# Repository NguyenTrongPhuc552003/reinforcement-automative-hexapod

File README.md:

## NOTE: This hexapod project is still under development and may not be fully functional. So, please wait for an official release is coming soon!

# Hexapod Robot Control System

A comprehensive control system for a six-legged robot (hexapod) using BeagleBone AI (or Black), featuring both kernel-space drivers and user-space applications with reinforcement learning capabilities.

<div align="center">

</div>

## Project Overview

This project implements a complete software stack for controlling a 6-legged robot with 18 servo motors (3 per leg), including:

- **Kernel-Space Components**:
  - Linux kernel driver for servo control (PCA9685 PWM controllers)
  - IMU sensor driver (MPU6050) for orientation sensing
  - Hardware abstraction layer for unified device access
  
- **User-Space Components**: 
  - Kinematics library for precise leg positioning
  - Gait generation for various walking patterns
  - Calibration system for mechanical offset compensation
  - Interactive control interface

- **Reinforcement Learning**:
  - TD3 (Twin Delayed Deep Deterministic Policy Gradient) implementation
  - Hardware acceleration via TIDL and OpenCL
  - Simulation-to-real transfer capabilities
  - On-robot inference engine

## System Architecture

The system follows a layered architecture with hardware abstraction. For visual reference, see the architecture diagrams in the `/docs/diagram/image` directory:

- [Deployment Diagram](docs/diagram/image/deployment.png): Hardware and software deployment
- [Component Diagram](docs/diagram/image/component.png): Hardware component interactions
- [Sequence Diagram](docs/diagram/image/sequence.png): Runtime interactions
- [State Diagram](docs/diagram/image/state.png): Hardware state transitions
- [Class Diagram](docs/diagram/image/class.png): Software class structure
- [Building Process](docs/diagram/image/building.png): Build and deployment process

```t
.
├── driver/          # Linux kernel device drivers
├── app/             # User applications and libraries
├── docs/            # Documentation
└── scripts/         # Build and utility scripts
```

## Features

- Multiple gait patterns (tripod, wave, ripple)
- Real-time IMU feedback
- Inverse kinematics for precise leg control
- Hardware abstraction layer
- Comprehensive test suite
- Interactive debugging tools

## Prerequisites

- BeagleBone Black (Rev C) running Linux Kernel 5.10+
- I2C enabled (bus 2)
- 18x servo motors (MG996R recommended)
- 1x MPU6050 IMU sensor
- 2x PCA9685 PWM controllers

## Quick Start

1. Build the kernel module:
   ```bash
   ./scripts/build.sh -b driver
   ```

2. Install the kernel module on BeagleBone Black:
   ```bash
   ./install.sh
   ```

3. Build user-space applications:
   ```bash
   ./scripts/build.sh -b app
   ```

4. Run the test utility on BeagleBone Black:
   ```bash
   ./test_servo
   ```

## Development

See individual README files in subdirectories for detailed development guides:
- [Kernel Driver README](driver/README.md)
- [User Space README](app/README.md)
- [Python TD3 README](pytd3/README.md)
- [Hardware Overview README](hardware/README.md)
- [Cross-compile Environment README](docker/README.md)
- [Documentation](docs/README.md)

## Testing

Individual tests:
```bash
./test_servo       # Test servo control
./test_mpu6050     # Test IMU sensor
./test_autonomous  # Test autonomous navigation
./test_calibration # Test servos offset for each leg
./test_hcsr04      # Test HC-SR04 sensor
```

## Troubleshooting

### Sensor Issues
- **Zero IMU readings**: The MPU6050 enters sleep mode to save power. The driver now automatically wakes it before readings.
- **Erratic IMU behavior**: Check I2C connections and ensure proper power supply voltage.

### Servo Issues
- **Servos not moving**: Check power supply and ensure driver is properly loaded
- **Erratic movement**: Verify calibration settings and check for loose connections

## Documentation

- [Hardware Setup](docs/overview/hardware.md)
- [Software Architecture](docs/overview/architecture.md)
- [Quick Start Guide](docs/overview/quickstart.md)

## Contributing

1. Fork the repository
2. Create a feature branch
3. Commit your changes
4. Push to the branch
5. Create a Pull Request

## License

This project is licensed under the terms of the GNU General Public License v2.0.

## Authors

- StrongFood - I mean **"TrongPhuc"**

## Acknowledgments

- BeagleBoard.org
- Linux Kernel Community

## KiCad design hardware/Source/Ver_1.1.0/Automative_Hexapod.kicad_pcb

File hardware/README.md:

## System Components

### 1. **BeagleBone Black (BBB)**
BeagleBone Black is used as the central processing unit, running Linux and handling all real-time control logic. It communicates with:
- **PCA9685 servo drivers** via I2C (SCL on P9.19, SDA on P9.20)
- **Ultrasonic sensor** via GPIO (TRIG on P8.11, ECHO on P8.12)
- **IMU (MPU6050)** via I2C

It also generates PWM signals and controls other peripherals (e.g., thermal fan).

---

### 2. **Servo Driver Modules**
Two PCA9685 chips are used as PWM generators to drive 16 of the 18 required servos (expandable). Each driver:
- Communicates with the BBB over I2C
- Outputs 8 independent PWM signals for servo motors
- Includes address pins (A0–A5) to support multiple drivers on the same I2C bus
- Contains decoupling capacitors and pull-up resistors for signal stability

---

### 3. **Ultrasonic Sensor (HC-SR04)**
The HC-SR04 sensor is used to detect obstacles and measure distance:
- Powered by +5V with decoupling capacitors (10uF and 100nF)
- Connected to BBB via:
  - TRIG pin (output from BBB)
  - ECHO pin (input to BBB, with level shifting for 3.3V compatibility)
- The data is used to decide turning or stopping actions

---

### 4. **IMU Sensor (MPU6050)**
- Provides orientation and acceleration feedback
- Connected via I2C (shared with other peripherals)
- Powered by +5V with local decoupling capacitors

---

### 5. **Power Supply Circuit**
- Accepts external battery input (+BATT) and generates regulated +5V and +3.3V
- Features buck converter (TPS54331DR) with appropriate filter networks
- Provides stable voltage rails to all system modules

---

### 6. **Level Shifting Circuit**
- Used to safely interface 5V logic (from HC-SR04 ECHO) with 3.3V logic of the BBB
- Implemented using MOSFET-based bidirectional level shifters
- Ensures reliable operation and protection of BBB GPIO pins

---

### 7. **Thermal Fan Driver**
- Controlled via PWM from BBB (PWM1A)
- Includes MOSFET switching and resistive control for speed regulation
- Provides thermal management for the electronics chassis if needed

---

### 8. **Servo Connectors Board**
- Groups and distributes servo outputs from the PCA9685 modules
- Adds additional bypass capacitors for local noise suppression
- Organized with labeled connectors for easy assembly

---

## Files and Schematics
The full KiCad schematic set includes:
- `Overview Schematic`
- `BBBlack.kicad_sch`
- `ServoDrivers.kicad_sch`
- `HC-SR04.kicad_sch`
- `IMU.kicad_sch`
- `PowerSupply.kicad_sch`
- `LevelShifting.kicad_sch`
- `ThermalFan.kicad_sch`
- `ConnectorServo.kicad_sch`

---

## Key Features
- 18 DOF hexapod locomotion with coordinated servo control
- Real-time obstacle detection using HC-SR04
- Modular design with clean separation of power, control, and sensing
- Compatible with Linux-based development on BeagleBone Black

---

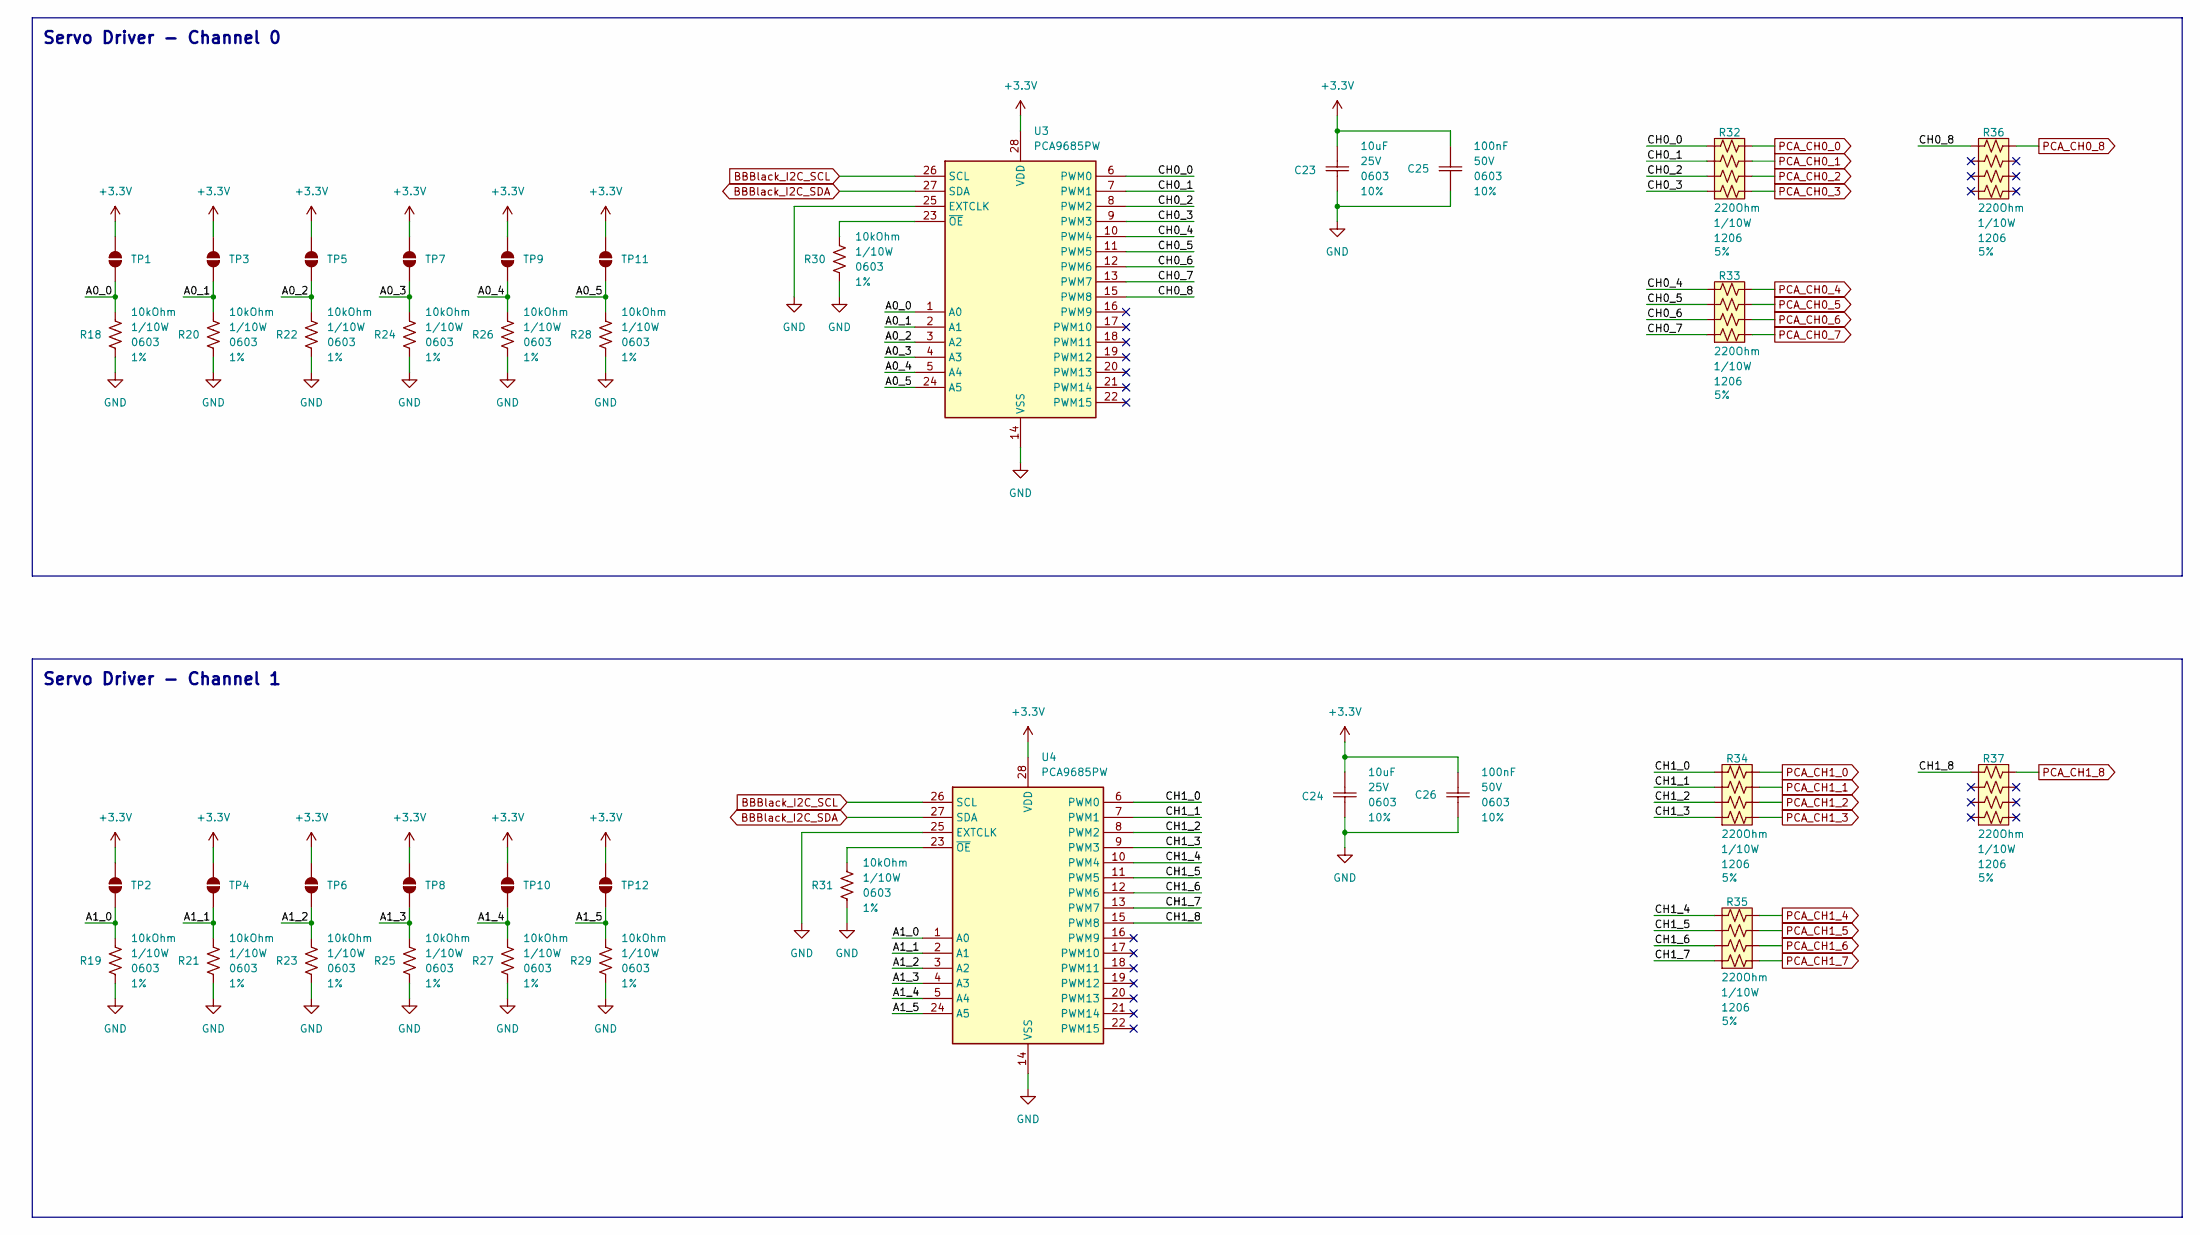
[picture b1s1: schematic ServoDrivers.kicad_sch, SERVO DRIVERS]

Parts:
C23, C24: 10uF; Ceramic_Cap_0603
C25, C26: 100nF; Ceramic_Cap_0603
R18, R19, R20, R21, R22, R23, R24, R25, R26, R27, R28, R29, R30, R31: 10kOhm; Res_0603
R32, R33, R34, R35, R36, R37: 220Ohm; R_Array_Convex_4x0603
TP1, TP2, TP3, TP4, TP5, TP6, TP7, TP8, TP9, TP10, TP11, TP12: SolderBridgeOpen
U3, U4: PCA9685PW; TSSOP-28_4.4x9.7mm_P0.65mm

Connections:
+3.3V: C23.2, C24.2, C25.2, C26.2, TP1.2, TP2.2, TP3.2, TP4.2, TP5.2, TP6.2, TP7.2, TP8.2, TP9.2, TP10.2, TP11.2, TP12.2, U3.28 (VDD), U4.28 (VDD); also elsewhere on the board
/Servo Drivers/A0_0: R18.2, TP1.1, U3.1 (A0)
/Servo Drivers/A0_1: R20.2, TP3.1, U3.2 (A1)
/Servo Drivers/A0_2: R22.2, TP5.1, U3.3 (A2)
/Servo Drivers/A0_3: R24.2, TP7.1, U3.4 (A3)
/Servo Drivers/A0_4: R26.2, TP9.1, U3.5 (A4)
/Servo Drivers/A0_5: R28.2, TP11.1, U3.24 (A5)
/Servo Drivers/A1_0: R19.2, TP2.1, U4.1 (A0)
/Servo Drivers/A1_1: R21.2, TP4.1, U4.2 (A1)
/Servo Drivers/A1_2: R23.2, TP6.1, U4.3 (A2)
/Servo Drivers/A1_3: R25.2, TP8.1, U4.4 (A3)
/Servo Drivers/A1_4: R27.2, TP10.1, U4.5 (A4)
/Servo Drivers/A1_5: R29.2, TP12.1, U4.24 (A5)
/Servo Drivers/CH0_0: R32.4, U3.6 (PWM0)
/Servo Drivers/CH0_1: R32.3, U3.7 (PWM1)
/Servo Drivers/CH0_2: R32.2, U3.8 (PWM2)
/Servo Drivers/CH0_3: R32.1, U3.9 (PWM3)
/Servo Drivers/CH0_4: R33.4, U3.10 (PWM4)
/Servo Drivers/CH0_5: R33.3, U3.11 (PWM5)
/Servo Drivers/CH0_6: R33.2, U3.12 (PWM6)
/Servo Drivers/CH0_7: R33.1, U3.13 (PWM7)
/Servo Drivers/CH0_8: R36.4, U3.15 (PWM8)
/Servo Drivers/CH1_0: R34.4, U4.6 (PWM0)
/Servo Drivers/CH1_1: R34.3, U4.7 (PWM1)
/Servo Drivers/CH1_2: R34.2, U4.8 (PWM2)
/Servo Drivers/CH1_3: R34.1, U4.9 (PWM3)
/Servo Drivers/CH1_4: R35.4, U4.10 (PWM4)
/Servo Drivers/CH1_5: R35.3, U4.11 (PWM5)
/Servo Drivers/CH1_6: R35.2, U4.12 (PWM6)
/Servo Drivers/CH1_7: R35.1, U4.13 (PWM7)
/Servo Drivers/CH1_8: R37.4, U4.15 (PWM8)
BBBlack_I2C_SCL: U3.26 (SCL), U4.26 (SCL); also elsewhere on the board
BBBlack_I2C_SDA: U3.27 (SDA), U4.27 (SDA); also elsewhere on the board
GND: C23.1, C24.1, C25.1, C26.1, R18.1, R19.1, R20.1, R21.1, R22.1, R23.1, R24.1, R25.1, R26.1, R27.1, R28.1, R29.1, R30.1, R31.1, U3.14 (VSS), U3.25 (EXTCLK), U4.14 (VSS), U4.25 (EXTCLK); also elsewhere on the board
unnamed: R30.2, U3.23 (~OE)
unnamed: R31.2, U4.23 (~OE)
PCA_CH0_0: R32.5; also elsewhere on the board
PCA_CH0_1: R32.6; also elsewhere on the board
PCA_CH0_2: R32.7; also elsewhere on the board
PCA_CH0_3: R32.8; also elsewhere on the board
PCA_CH0_4: R33.5; also elsewhere on the board
PCA_CH0_5: R33.6; also elsewhere on the board
PCA_CH0_6: R33.7; also elsewhere on the board
PCA_CH0_7: R33.8; also elsewhere on the board
PCA_CH0_8: R36.5; also elsewhere on the board
PCA_CH1_0: R34.5; also elsewhere on the board
PCA_CH1_1: R34.6; also elsewhere on the board
PCA_CH1_2: R34.7; also elsewhere on the board
PCA_CH1_3: R34.8; also elsewhere on the board
PCA_CH1_4: R35.5; also elsewhere on the board
PCA_CH1_5: R35.6; also elsewhere on the board
PCA_CH1_6: R35.7; also elsewhere on the board
PCA_CH1_7: R35.8; also elsewhere on the board
PCA_CH1_8: R37.5; also elsewhere on the board

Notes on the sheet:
Servo Driver - Channel 1
Servo Driver - Channel 0

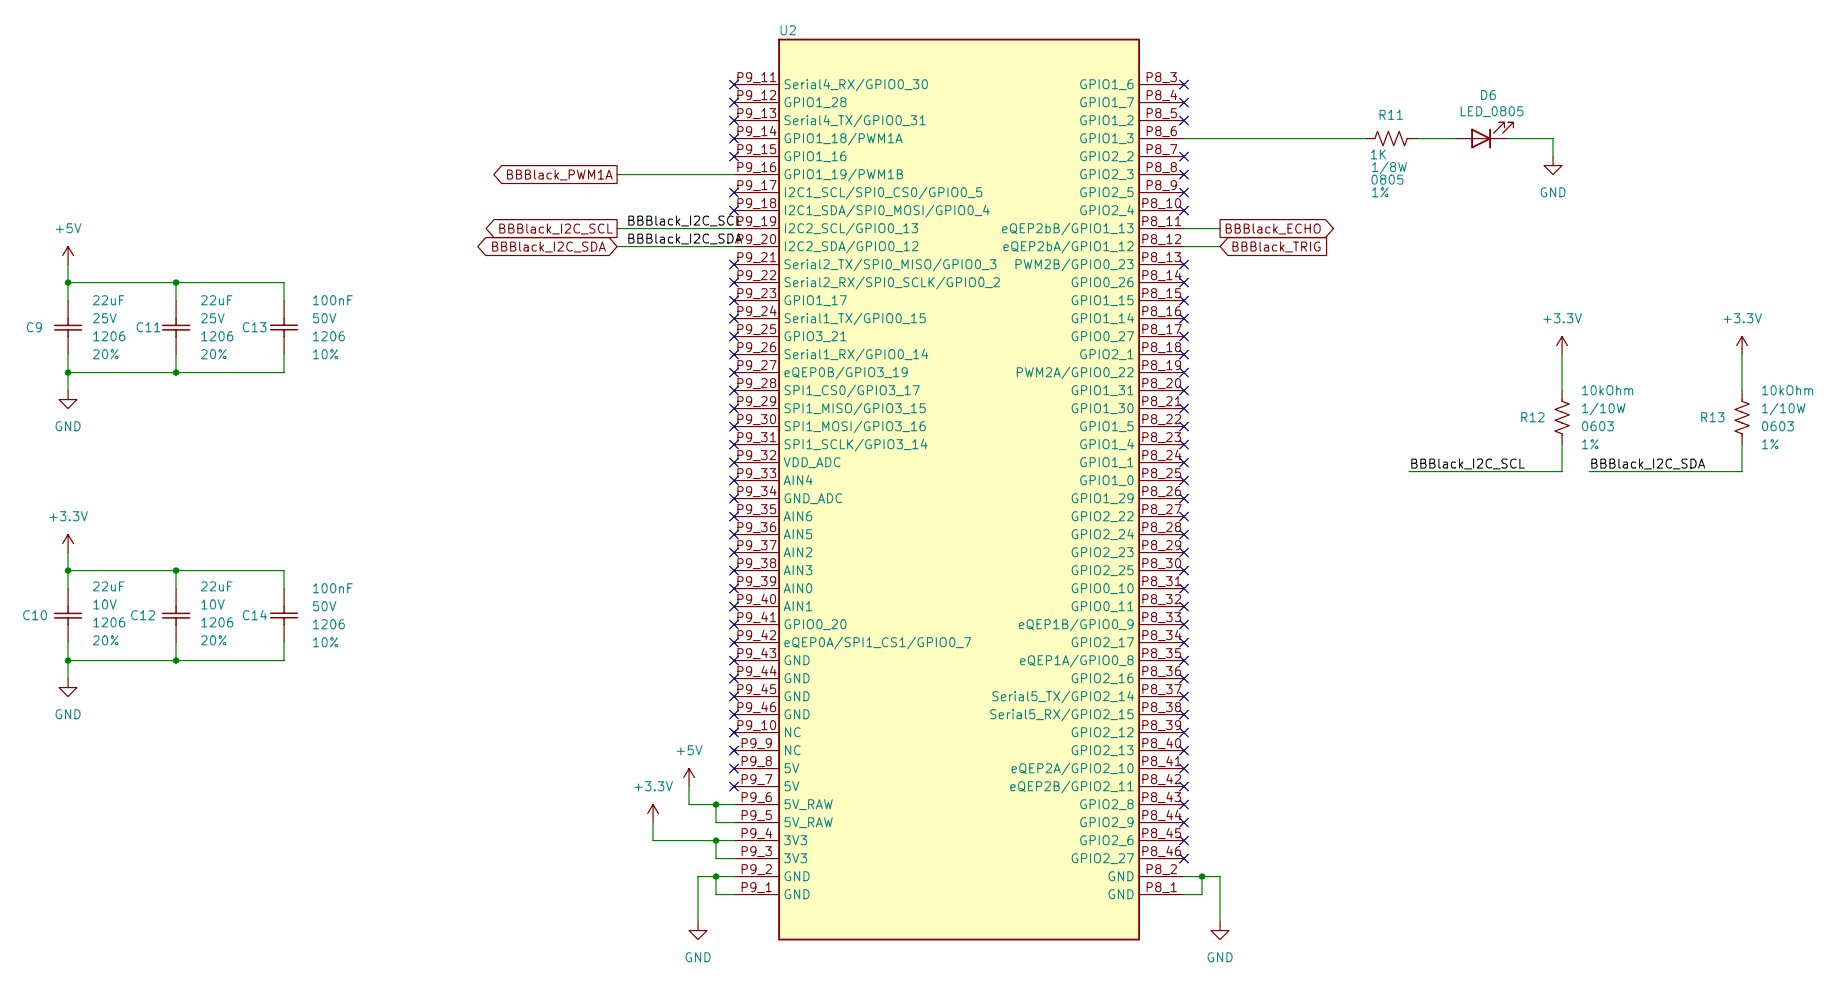
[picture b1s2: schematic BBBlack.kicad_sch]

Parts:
C9, C10, C11, C12: 22uF; Ceramic_Cap_1206
C13, C14: 100nF; Ceramic_Cap_1206
D6: LED_0805
R11: 1K; Res_0805
R12, R13: 10kOhm; Res_0603
U2: BeagleBone_AI

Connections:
+3.3V: C10.2, C12.2, C14.1, R12.2, R13.2, U2.P9_3 (3V3), U2.P9_4 (3V3); also elsewhere on the board
+5V: C9.2, C11.2, C13.1, U2.P9_5 (5V_RAW), U2.P9_6 (5V_RAW); also elsewhere on the board
BBBlack_ECHO: U2.P8_11 (eQEP2bB/GPIO1_13); also elsewhere on the board
BBBlack_I2C_SCL: R12.1, U2.P9_19 (I2C2_SCL/GPIO0_13); also elsewhere on the board
BBBlack_I2C_SDA: R13.1, U2.P9_20 (I2C2_SDA/GPIO0_12); also elsewhere on the board
BBBlack_PWM1A: U2.P9_16 (GPIO1_19/PWM1B); also elsewhere on the board
BBBlack_TRIG: U2.P8_12 (eQEP2bA/GPIO1_12); also elsewhere on the board
GND: C9.1, C10.1, C11.1, C12.1, C13.2, C14.2, D6.1 (K), U2.P8_1 (GND), U2.P8_2 (GND), U2.P9_1 (GND), U2.P9_2 (GND); also elsewhere on the board
unnamed: D6.2 (A), R11.2
unnamed: R11.1, U2.P8_6 (GPIO1_3)

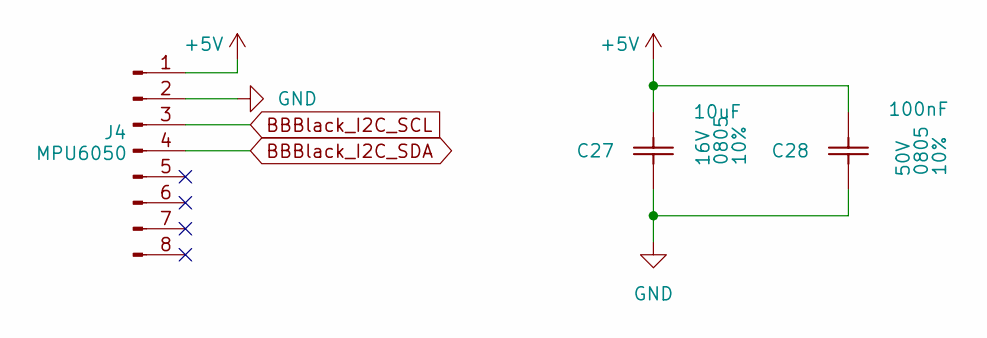
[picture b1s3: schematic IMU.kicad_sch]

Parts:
C27: 10uF; Ceramic_Cap_0805
C28: 100nF; Ceramic_Cap_0805
J4: MPU6050

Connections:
+5V: C27.2, C28.2, J4.1; also elsewhere on the board
BBBlack_I2C_SCL: J4.3; also elsewhere on the board
BBBlack_I2C_SDA: J4.4; also elsewhere on the board
GND: C27.1, C28.1, J4.2; also elsewhere on the board

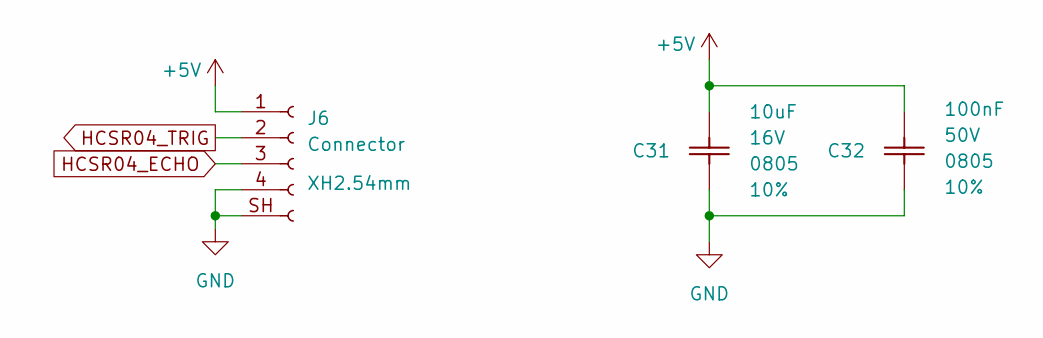
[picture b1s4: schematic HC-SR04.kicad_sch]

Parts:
C31: 10uF; Ceramic_Cap_0805
C32: 100nF; Ceramic_Cap_0805
J6: Connector; JST-XH-SMD-4-2.54mm

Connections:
+5V: C31.2, C32.2, J6.1; also elsewhere on the board
GND: C31.1, C32.1, J6.4, J6.SH (Pin_3); also elsewhere on the board
HCSR04_ECHO: J6.3; also elsewhere on the board
HCSR04_TRIG: J6.2; also elsewhere on the board

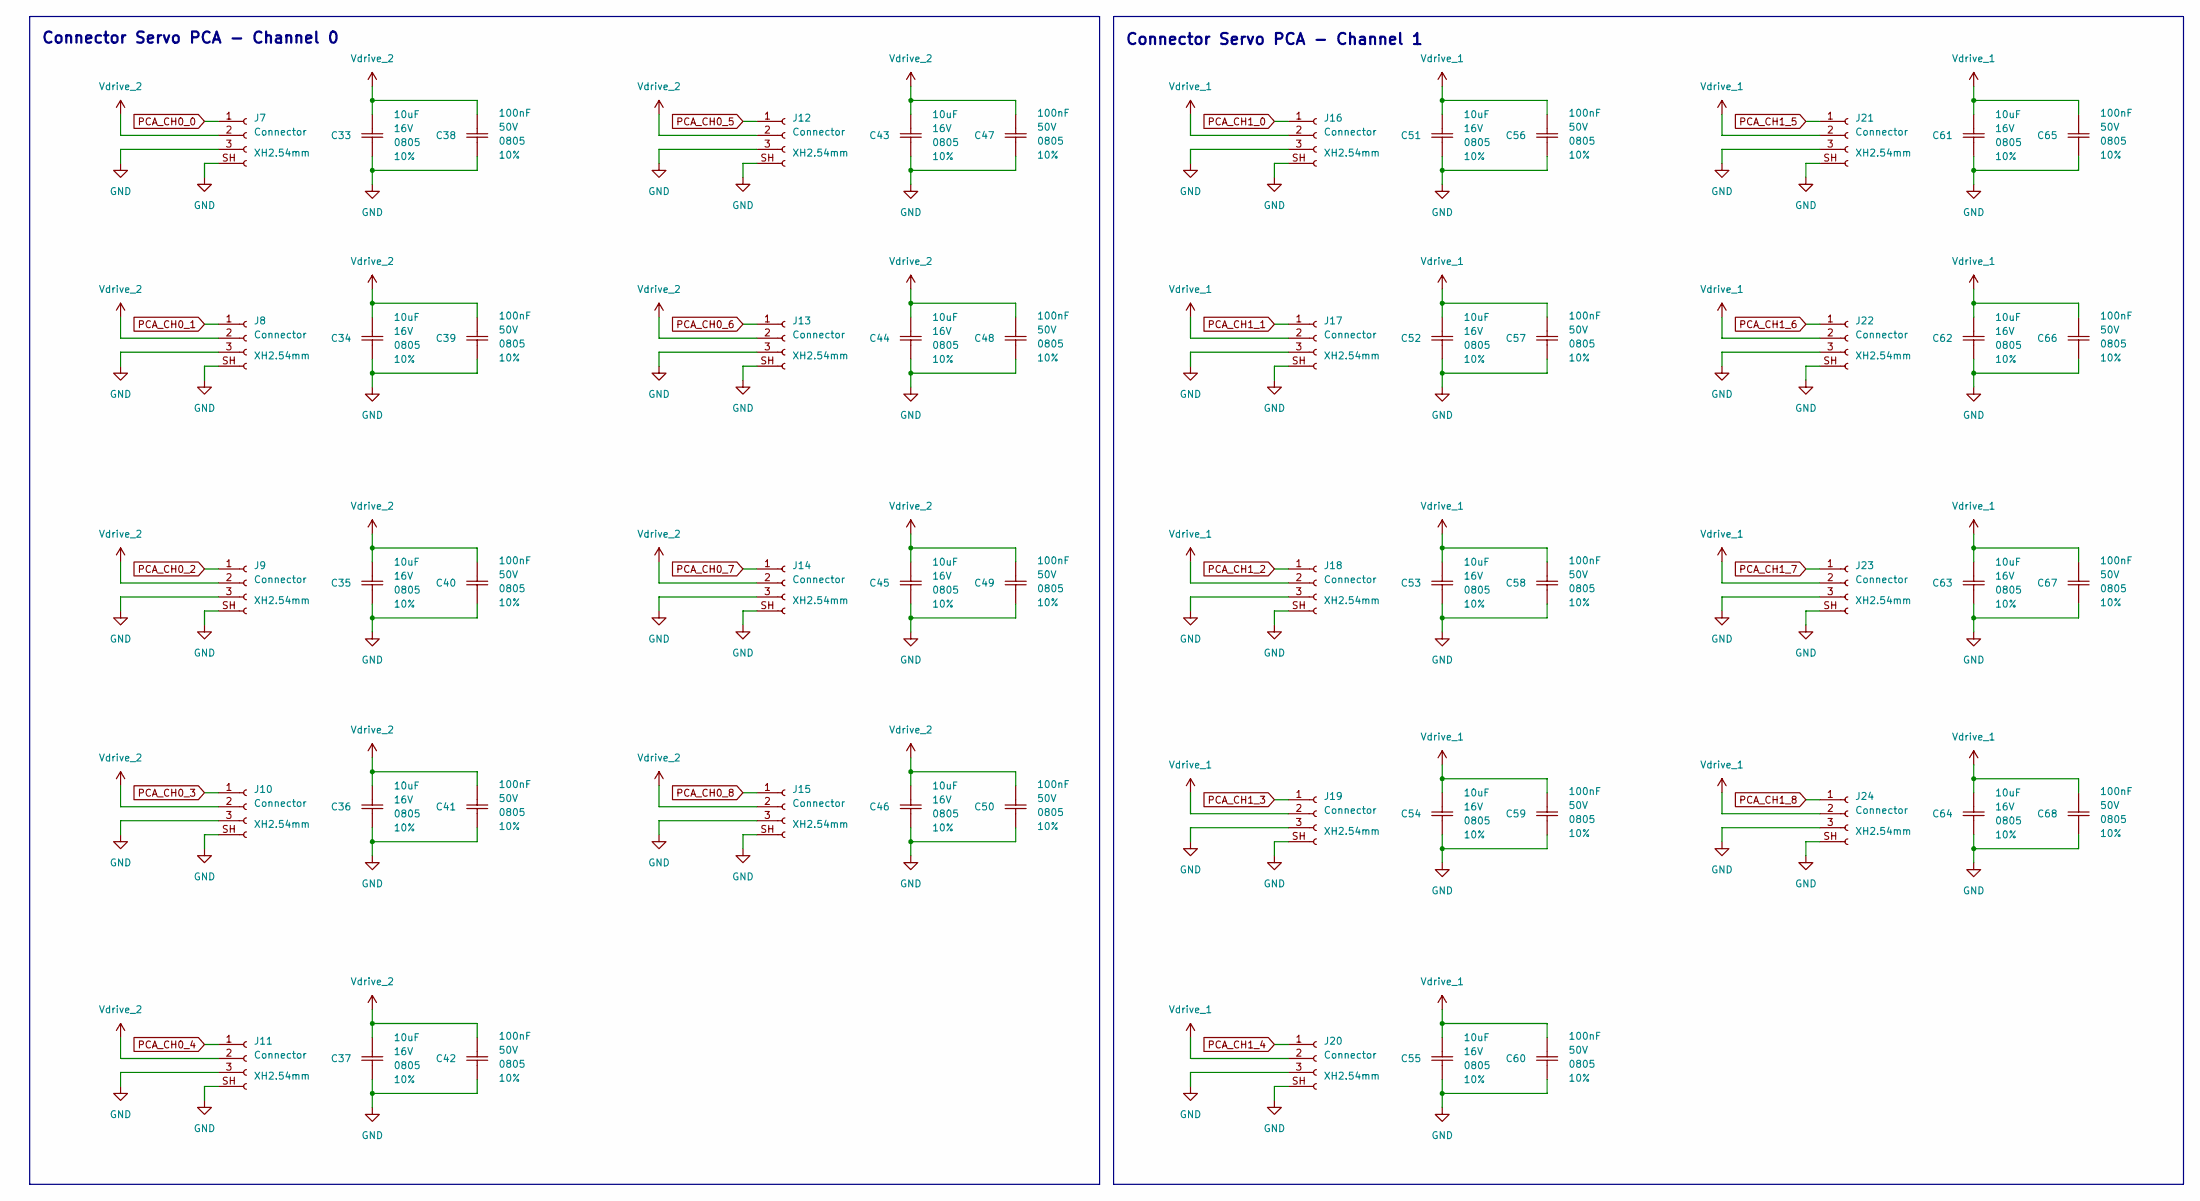
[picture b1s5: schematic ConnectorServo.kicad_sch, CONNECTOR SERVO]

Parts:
C33, C34, C35, C36, C37, C43, C44, C45, C46, C51, C52, C53, C54, C55, C61, C62, C63, C64: 10uF; Ceramic_Cap_0805
C38, C39, C40, C41, C42, C47, C48, C49, C50, C56, C57, C58, C59, C60, C65, C66, C67, C68: 100nF; Ceramic_Cap_0805
J7, J8, J9, J10, J11, J12, J13, J14, J15, J16, J17, J18, J19, J20, J21, J22, J23, J24: Connector; JST-XH-SMD-3-2.54mm

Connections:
GND: C33.1, C34.1, C35.1, C36.1, C37.1, C38.1, C39.1, C40.1, C41.1, C42.1, C43.1, C44.1, C45.1, C46.1, C47.1, C48.1, C49.1, C50.1, C51.1, C52.1, C53.1, C54.1, C55.1, C56.1, C57.1, C58.1, C59.1, C60.1, C61.1, C62.1, C63.1, C64.1, C65.1, C66.1, C67.1, C68.1, J7.3, J7.SH (Pin_3), J8.3, J8.SH (Pin_3), J9.3, J9.SH (Pin_3), J10.3, J10.SH (Pin_3), J11.3, J11.SH (Pin_3), J12.3, J12.SH (Pin_3), J13.3, J13.SH (Pin_3), J14.3, J14.SH (Pin_3), J15.3, J15.SH (Pin_3), J16.3, J16.SH (Pin_3), J17.3, J17.SH (Pin_3), J18.3, J18.SH (Pin_3), J19.3, J19.SH (Pin_3), J20.3, J20.SH (Pin_3), J21.3, J21.SH (Pin_3), J22.3, J22.SH (Pin_3), J23.3, J23.SH (Pin_3), J24.3, J24.SH (Pin_3); also elsewhere on the board
PCA_CH0_0: J7.1; also elsewhere on the board
PCA_CH0_1: J8.1; also elsewhere on the board
PCA_CH0_2: J9.1; also elsewhere on the board
PCA_CH0_3: J10.1; also elsewhere on the board
PCA_CH0_4: J11.1; also elsewhere on the board
PCA_CH0_5: J12.1; also elsewhere on the board
PCA_CH0_6: J13.1; also elsewhere on the board
PCA_CH0_7: J14.1; also elsewhere on the board
PCA_CH0_8: J15.1; also elsewhere on the board
PCA_CH1_0: J16.1; also elsewhere on the board
PCA_CH1_1: J17.1; also elsewhere on the board
PCA_CH1_2: J18.1; also elsewhere on the board
PCA_CH1_3: J19.1; also elsewhere on the board
PCA_CH1_4: J20.1; also elsewhere on the board
PCA_CH1_5: J21.1; also elsewhere on the board
PCA_CH1_6: J22.1; also elsewhere on the board
PCA_CH1_7: J23.1; also elsewhere on the board
PCA_CH1_8: J24.1; also elsewhere on the board
Vdrive_1: C51.2, C52.2, C53.2, C54.2, C55.2, C56.2, C57.2, C58.2, C59.2, C60.2, C61.2, C62.2, C63.2, C64.2, C65.2, C66.2, C67.2, C68.2, J16.2, J17.2, J18.2, J19.2, J20.2, J21.2, J22.2, J23.2, J24.2; also elsewhere on the board
Vdrive_2: C33.2, C34.2, C35.2, C36.2, C37.2, C38.2, C39.2, C40.2, C41.2, C42.2, C43.2, C44.2, C45.2, C46.2, C47.2, C48.2, C49.2, C50.2, J7.2, J8.2, J9.2, J10.2, J11.2, J12.2, J13.2, J14.2, J15.2; also elsewhere on the board

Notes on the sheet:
Connector Servo PCA - Channel 0
Connector Servo PCA - Channel 1

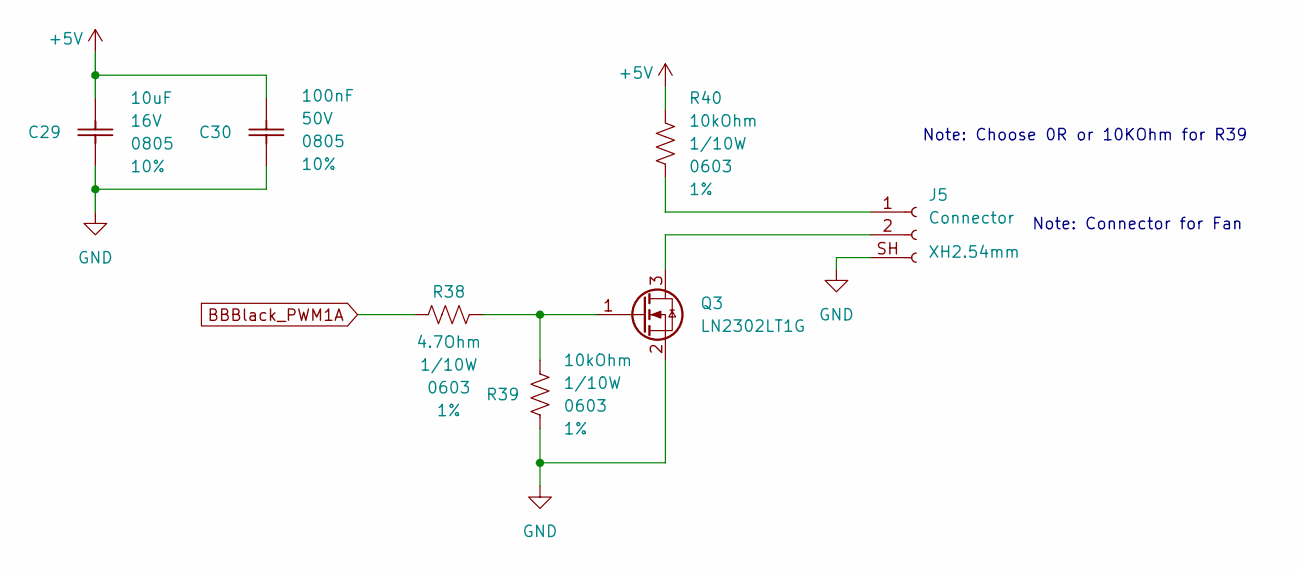
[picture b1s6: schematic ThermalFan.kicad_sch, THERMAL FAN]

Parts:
C29: 10uF; Ceramic_Cap_0805
C30: 100nF; Ceramic_Cap_0805
J5: Connector; JST-XH-SMD-2-2.54mm
Q3: LN2302LT1G; SOT23
R38: 4.7Ohm; Res_0603
R39, R40: 10kOhm; Res_0603

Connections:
+5V: C29.2, C30.2, R40.2; also elsewhere on the board
BBBlack_PWM1A: R38.1; also elsewhere on the board
GND: C29.1, C30.1, J5.SH (Pin_3), Q3.2 (S), R39.1; also elsewhere on the board
unnamed: J5.1, R40.1
unnamed: J5.2, Q3.3 (D)
unnamed: Q3.1 (G), R38.2, R39.2

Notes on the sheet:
Note: Connector for Fan
Note: Choose 0R or 10KOhm for R39

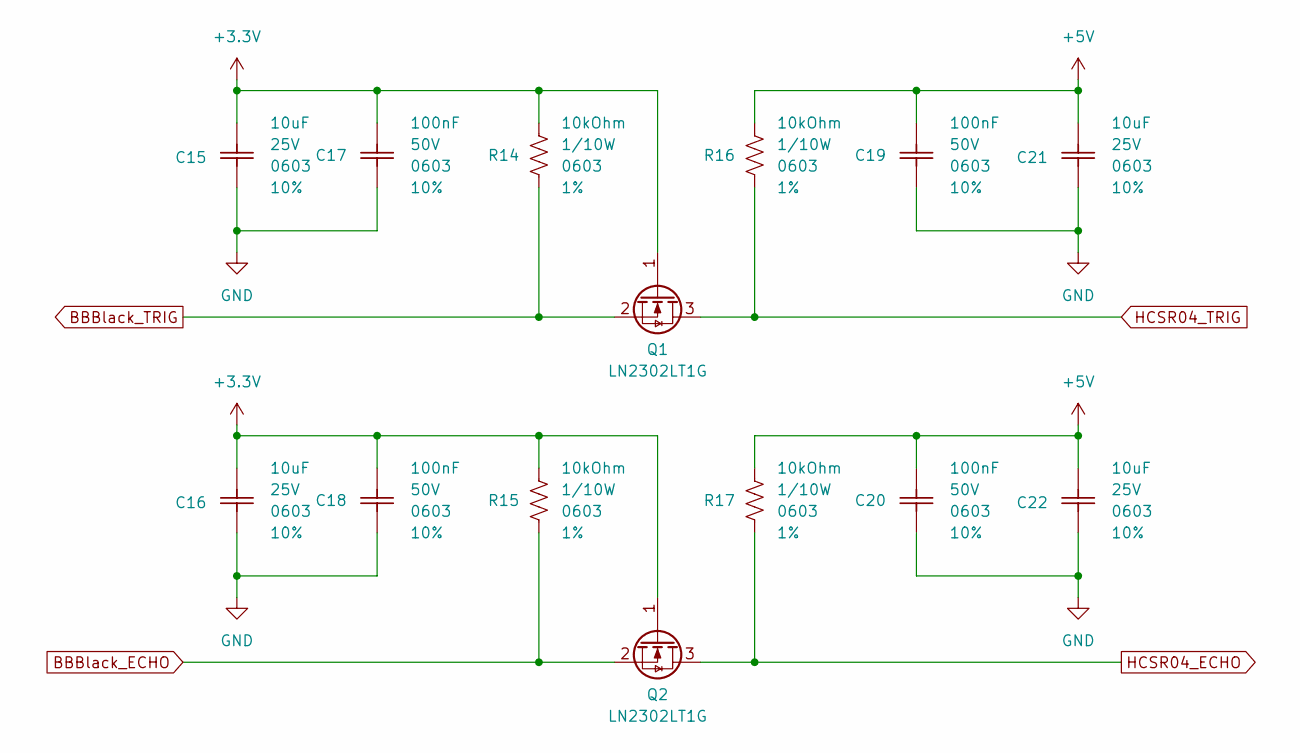
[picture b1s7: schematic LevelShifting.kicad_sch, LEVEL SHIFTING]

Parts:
C15, C16, C21, C22: 10uF; Ceramic_Cap_0603
C17, C18, C19, C20: 100nF; Ceramic_Cap_0603
Q1, Q2: LN2302LT1G; SOT23
R14, R15, R16, R17: 10kOhm; Res_0603

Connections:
+3.3V: C15.2, C16.2, C17.2, C18.2, Q1.1 (G), Q2.1 (G), R14.2, R15.2; also elsewhere on the board
+5V: C19.2, C20.2, C21.2, C22.2, R16.2, R17.2; also elsewhere on the board
BBBlack_ECHO: Q2.2 (S), R15.1; also elsewhere on the board
BBBlack_TRIG: Q1.2 (S), R14.1; also elsewhere on the board
GND: C15.1, C16.1, C17.1, C18.1, C19.1, C20.1, C21.1, C22.1; also elsewhere on the board
HCSR04_ECHO: Q2.3 (D), R17.1; also elsewhere on the board
HCSR04_TRIG: Q1.3 (D), R16.1; also elsewhere on the board

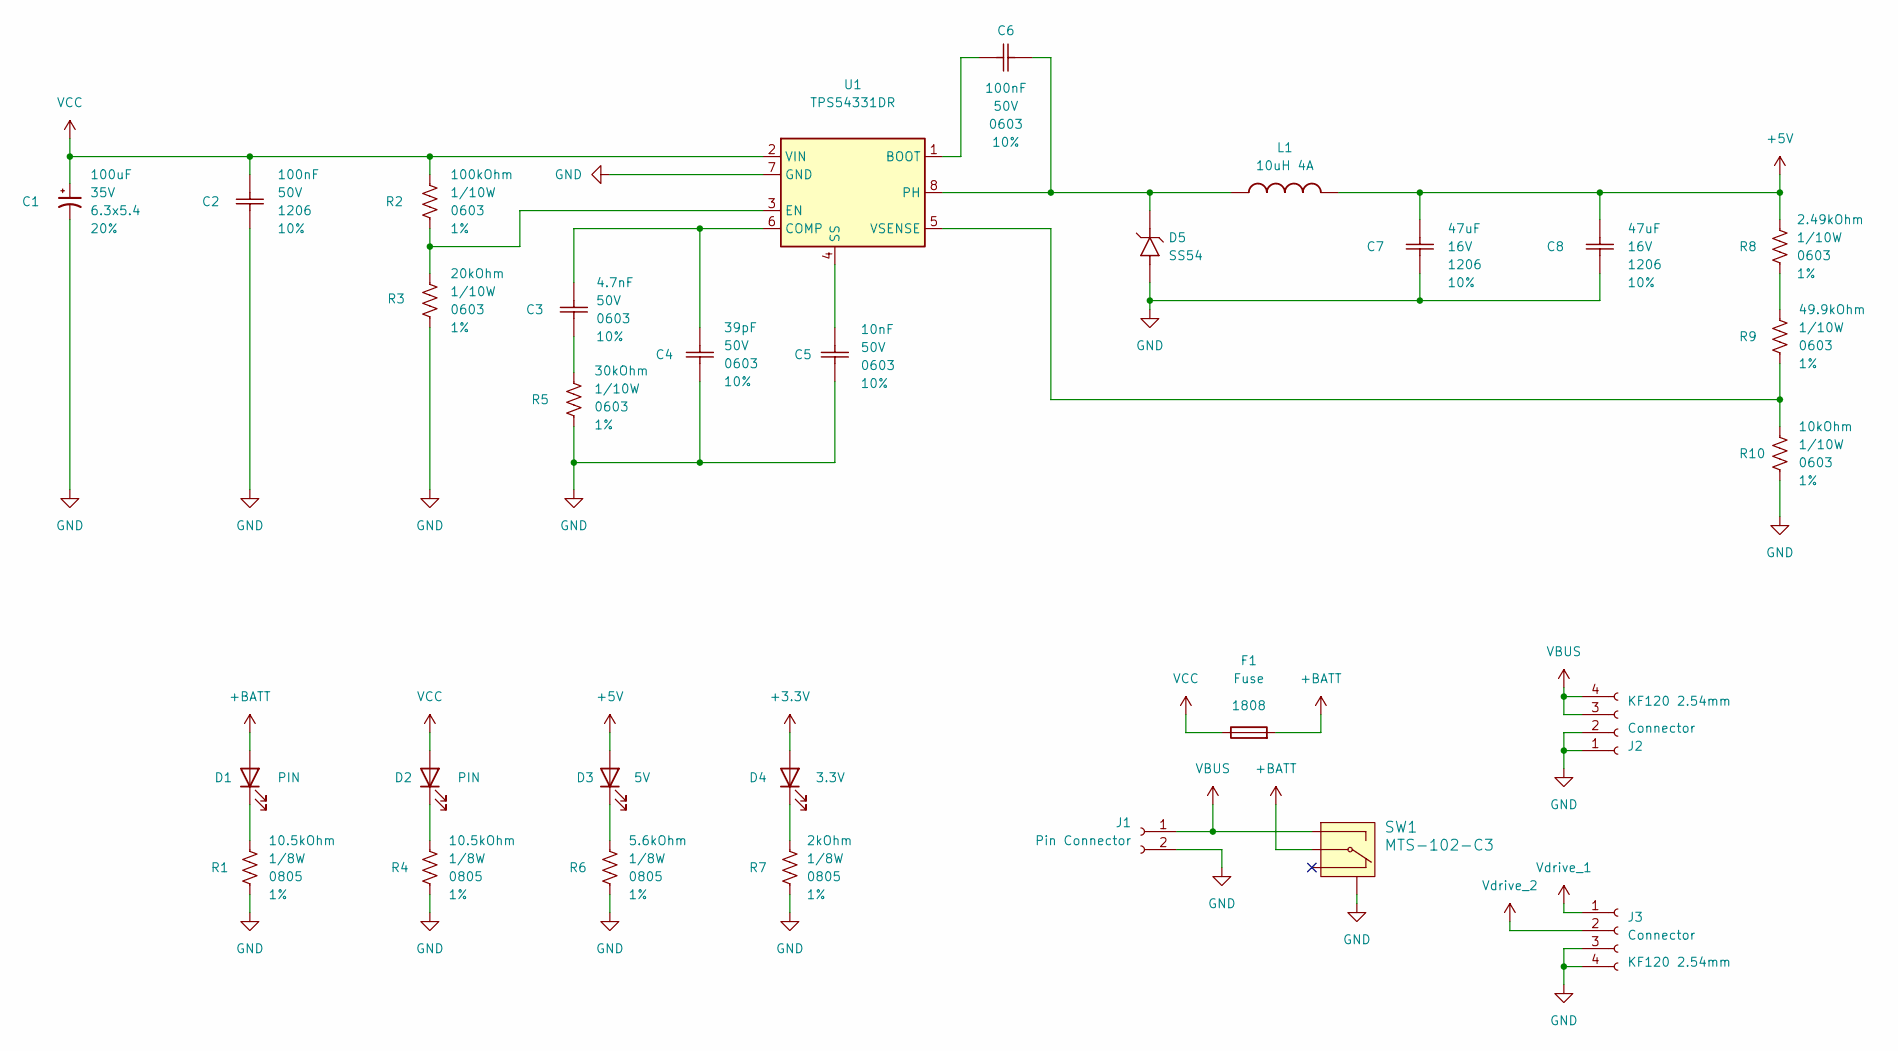
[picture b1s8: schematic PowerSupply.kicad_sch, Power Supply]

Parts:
C1: 100uF; CP_Elec_6.3x5.4
C2: 100nF; Ceramic_Cap_1206
C3: 4.7nF; Ceramic_Cap_0603
C4: 39pF; Ceramic_Cap_0603
C5: 10nF; Ceramic_Cap_0603
C6: 100nF; Ceramic_Cap_0603
C7, C8: 47uF; Ceramic_Cap_1206
D1, D2: PIN; LED_0805
D3: 5V; LED_0805
D4: 3.3V; LED_0805
D5: SS54; D_SMA
F1: Fuse; FUSE_SMD_1808
J1: Pin Connector; Connector-Pin
J2, J3: Connector; TerminalBlock_Phoenix_MKDS-1,5-4-5.08_1x04_P5.08mm_Horizont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
L1: 10uH 4A; Inductor_0630
R1, R4: 10.5kOhm; Res_0805
R2: 100kOhm; Res_0603
R3: 20kOhm; Res_0603
R5: 30kOhm; Res_0603
R6: 5.6kOhm; Res_0805
R7: 2kOhm; Res_0805
R8: 2.49kOhm; Res_0603
R9: 49.9kOhm; Res_0603
R10: 10kOhm; Res_0603
SW1: MTS-102-C3
U1: TPS54331DR; SOIC-8

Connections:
+3.3V: D4.2 (A); also elsewhere on the board
+5V: C7.2, C8.2, D3.2 (A), L1.2, R8.2; also elsewhere on the board
+BATT: D1.2 (A), F1.2, SW1.2
GND: C1.2, C2.2, C4.1, C5.1, C7.1, C8.1, D5.1 (A), J1.2, J2.1, J2.2, J3.3, J3.4, R1.1, R3.1, R4.1, R5.1, R6.1, R7.1, R10.1, SW1.SH, U1.7 (GND); also elsewhere on the board
unnamed: C3.1, R5.2
unnamed: D1.1 (K), R1.2
unnamed: D2.1 (K), R4.2
unnamed: D3.1 (K), R6.2
unnamed: D4.1 (K), R7.2
unnamed: C6.2, D5.2 (K), L1.1, U1.8 (PH)
unnamed: R8.1, R9.2
unnamed: C6.1, U1.1 (BOOT)
unnamed: C3.2, C4.2, U1.6 (COMP)
unnamed: R2.1, R3.2, U1.3 (EN)
unnamed: C5.2, U1.4 (SS)
unnamed: R9.1, R10.2, U1.5 (VSENSE)
VBUS: J1.1, J2.3, J2.4, SW1.3
VCC: C1.1, C2.1, D2.2 (A), F1.1, R2.2, U1.2 (VIN)
Vdrive_1: J3.1; also elsewhere on the board
Vdrive_2: J3.2; also elsewhere on the board

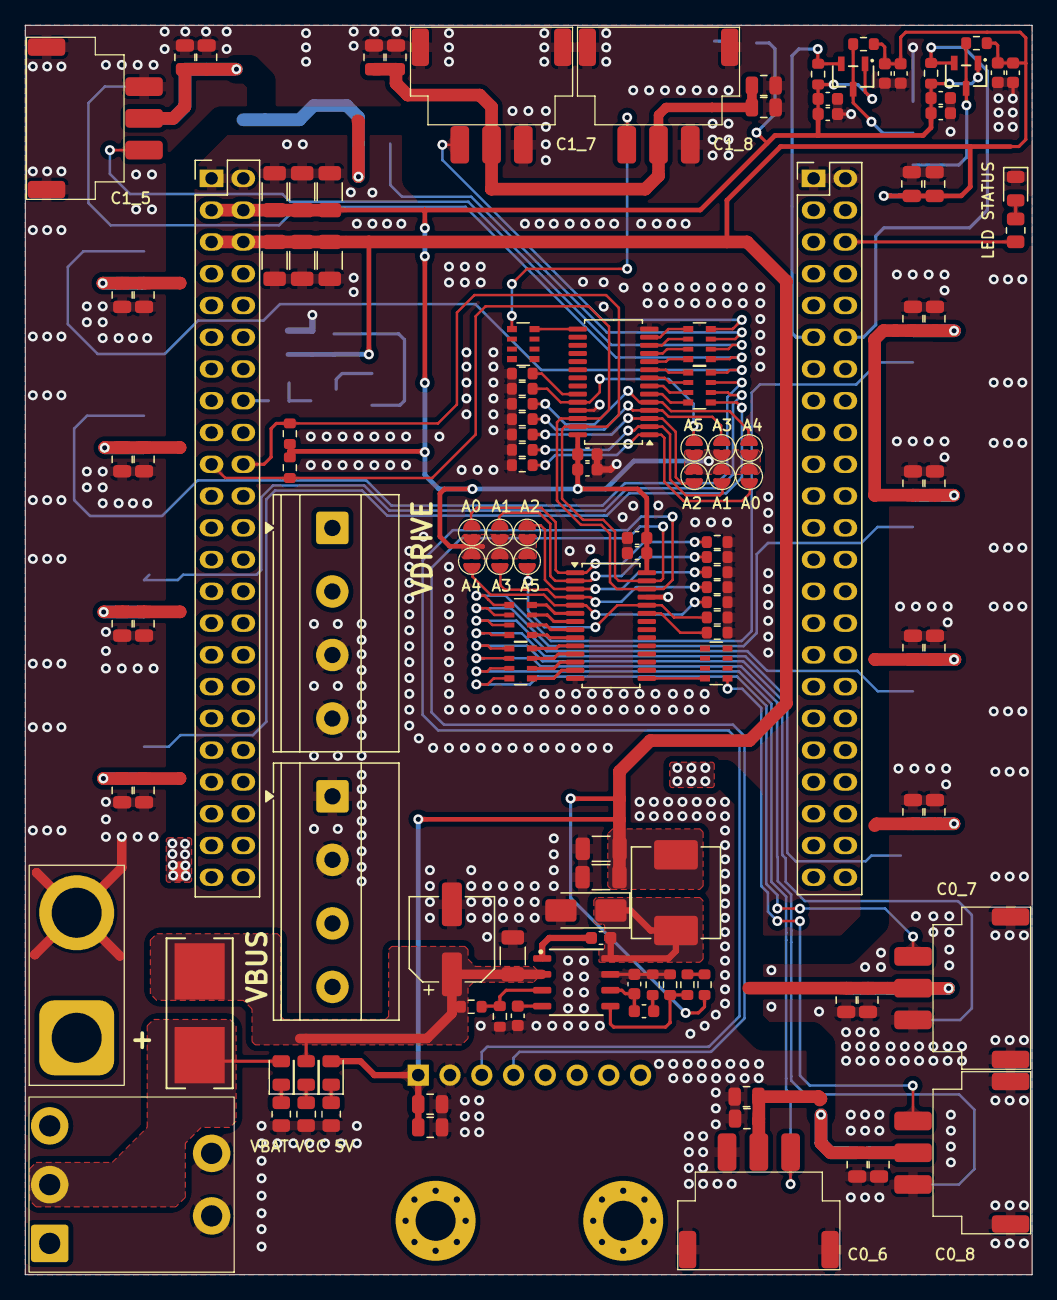
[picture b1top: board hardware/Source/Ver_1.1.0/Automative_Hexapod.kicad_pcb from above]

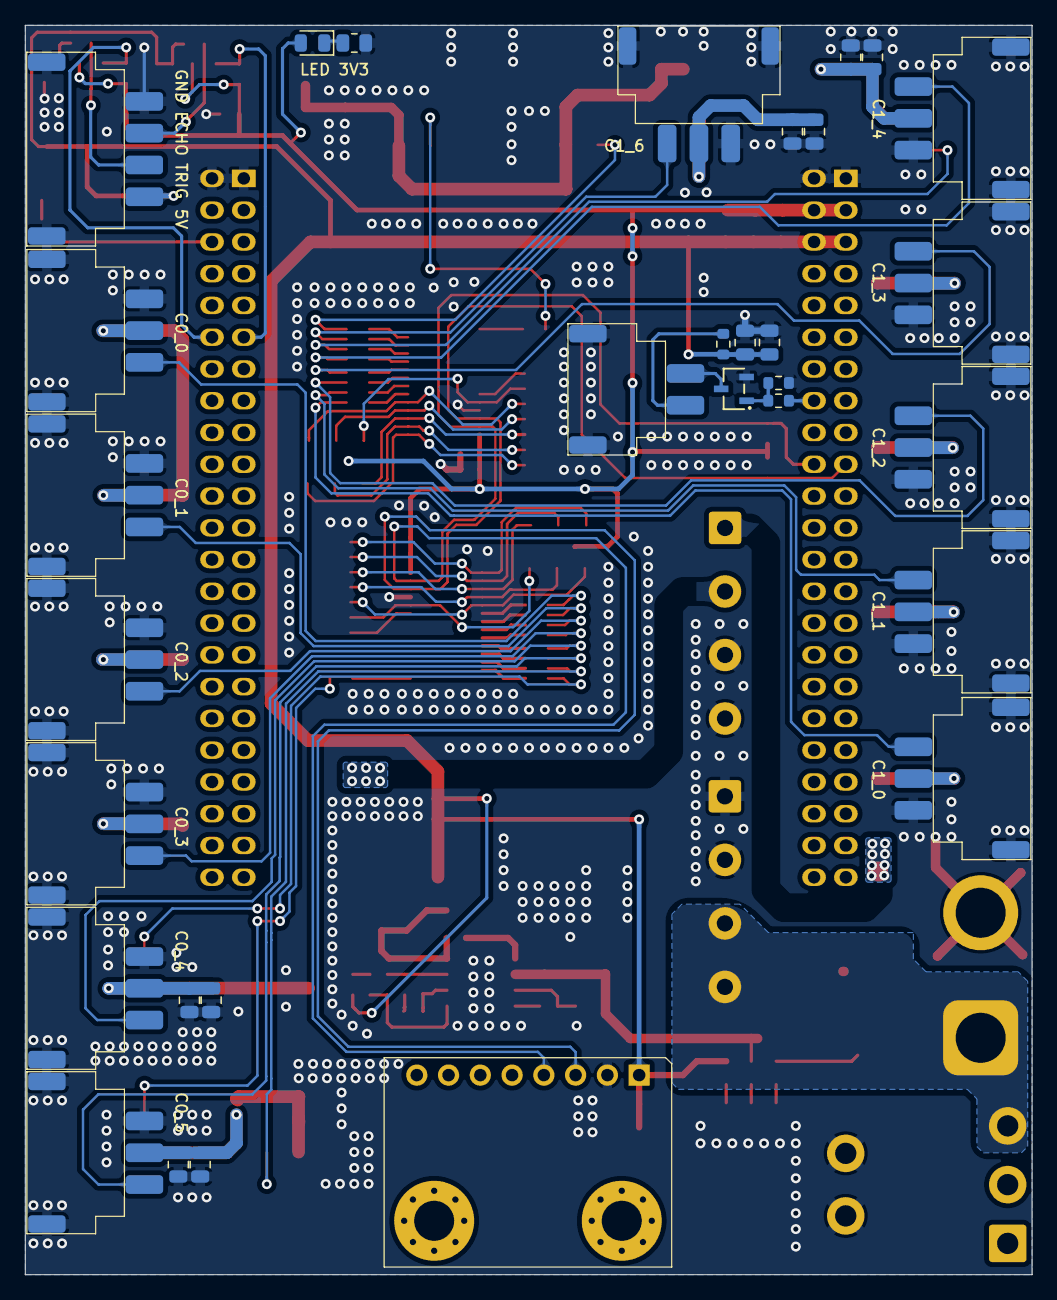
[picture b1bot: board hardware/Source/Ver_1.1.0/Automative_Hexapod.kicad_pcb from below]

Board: 2 copper layers, 80.5 x 99.9 mm, 160 parts (31 on the bottom side), 82 nets.
